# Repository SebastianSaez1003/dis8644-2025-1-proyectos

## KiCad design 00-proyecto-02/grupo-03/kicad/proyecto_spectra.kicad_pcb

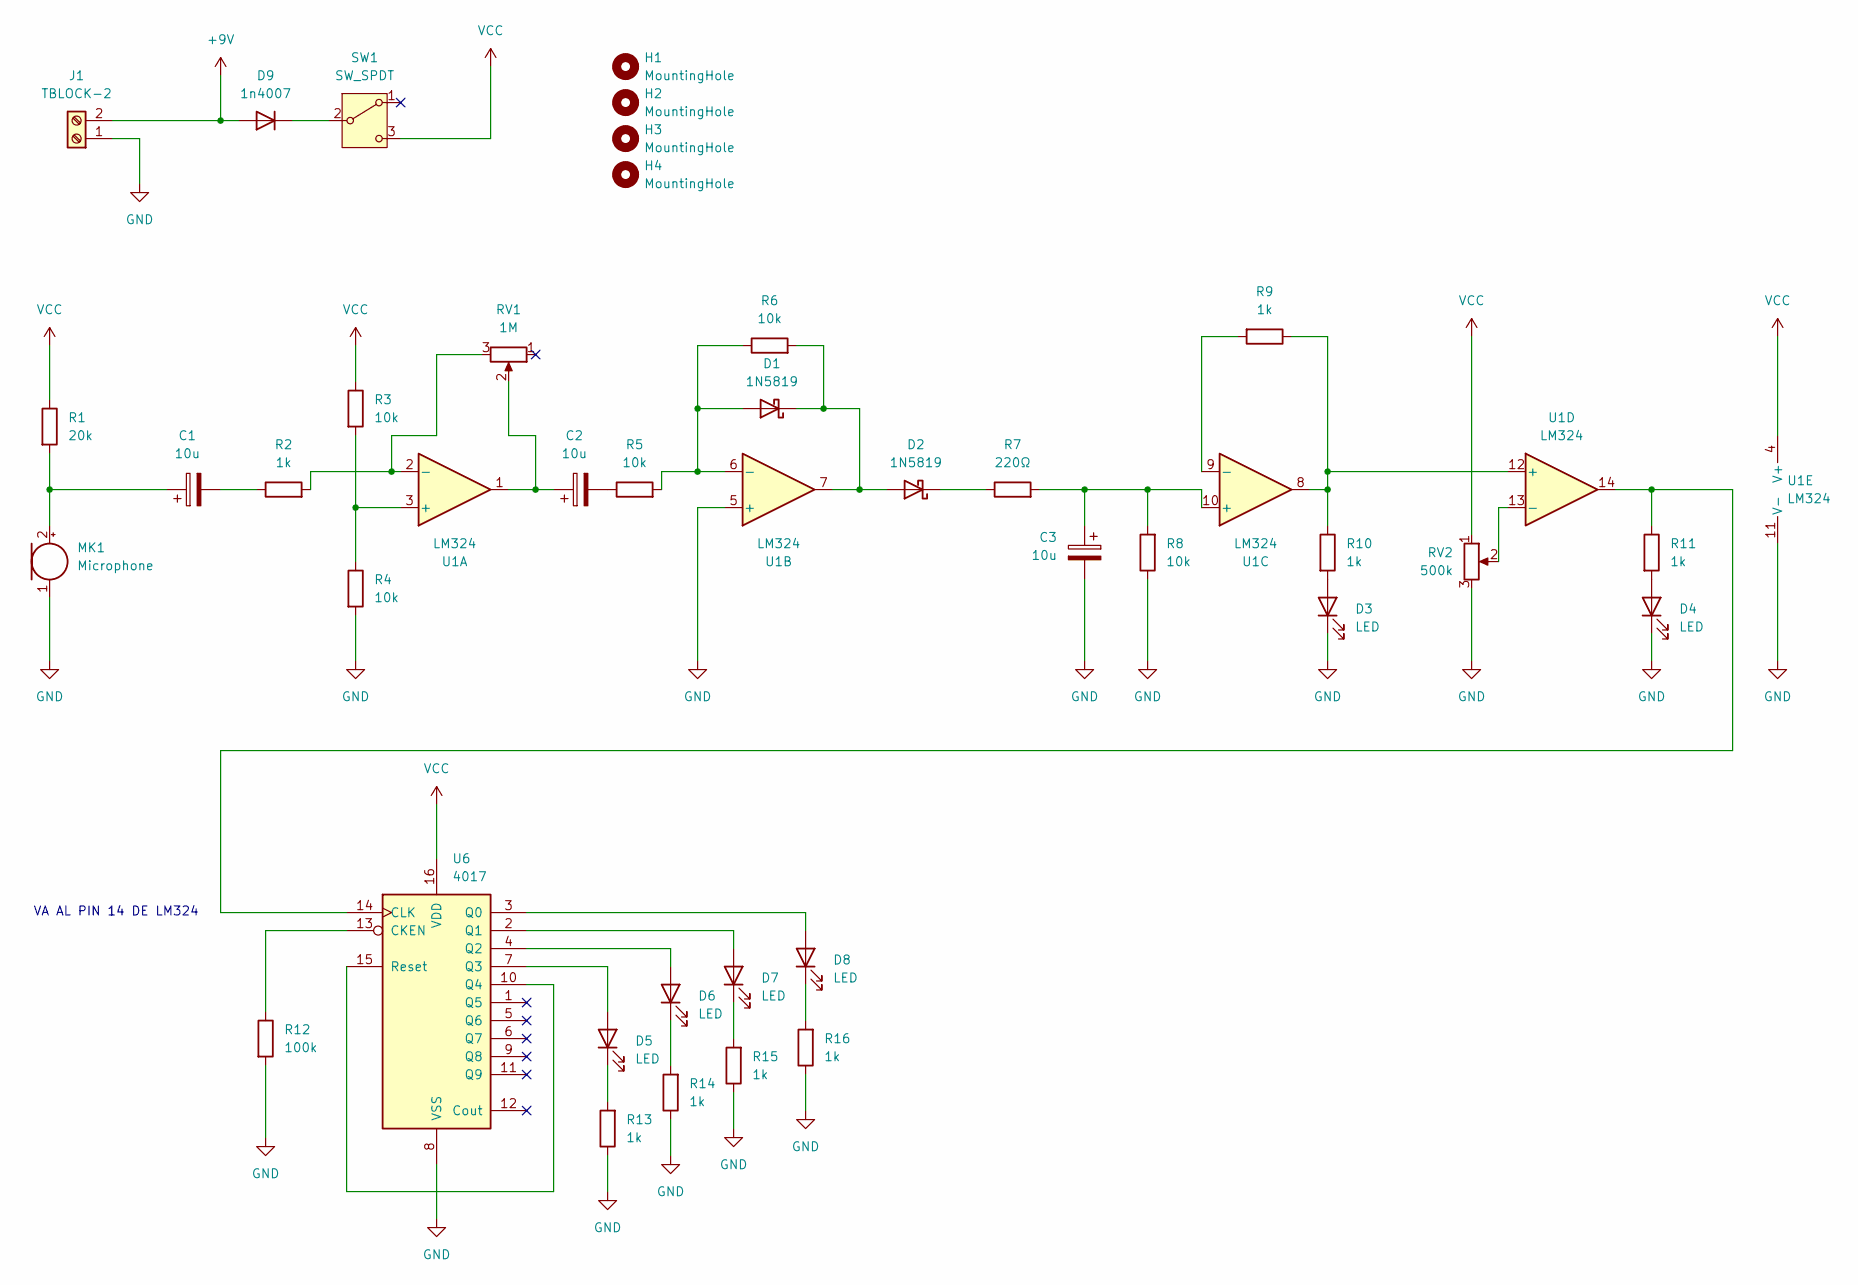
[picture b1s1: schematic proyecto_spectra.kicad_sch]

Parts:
C1, C2, C3: 10u; CP_Radial_D4.0mm_P2.00mm
D1, D2: 1N5819; D_DO-41_SOD81_P10.16mm_Horizontal
D3, D4, D5, D6, D7, D8: LED; LED_D5.0mm
D9: 1n4007; D_DO-41_SOD81_P10.16mm_Horizontal
H1, H2, H3, H4: MountingHole; MountingHole_2.1mm
J1: TBLOCK-2; TerminalBlock_MaiXu_MX126-5.0-02P_1x02_P5.00mm
MK1: Microphone; POM-2244P-C3310-2-R
R1: 20k; R_Axial_DIN0204_L3.6mm_D1.6mm_P5.08mm_Horizontal
R2, R9, R10, R11, R13, R14, R15, R16: 1k; R_Axial_DIN0204_L3.6mm_D1.6mm_P5.08mm_Horizontal
R3, R4, R5, R6, R8: 10k; R_Axial_DIN0204_L3.6mm_D1.6mm_P5.08mm_Horizontal
R7: 220Ω; R_Axial_DIN0204_L3.6mm_D1.6mm_P5.08mm_Horizontal
R12: 100k; R_Axial_DIN0204_L3.6mm_D1.6mm_P5.08mm_Horizontal
RV1: 1M; Potentiometer_Piher_T-16H_Single_Horizontal
RV2: 500k; Potentiometer_Piher_T-16H_Single_Horizontal
SW1: SW_SPDT; SPDT_PCB_small_P2.5mm
U1: LM324; DIP-14_W7.62mm
U6: 4017; DIP-16_W7.62mm

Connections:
+9V: D9.2 (A), J1.2
GND: C3.2, D3.1 (K), D4.1 (K), J1.1, MK1.1 (-), R4.2, R8.1, R12.2, R13.1, R14.1, R15.1, R16.1, RV2.3, U1.5 (+), U1.11 (V-), U6.8 (VSS)
unnamed: C1.2, R2.1
unnamed: C2.1, RV1.2, U1.1
unnamed: C2.2, R5.1
unnamed: D1.2 (A), R5.2, R6.1, U1.6 (-)
unnamed: D1.1 (K), D2.2 (A), R6.2, U1.7
unnamed: D2.1 (K), R7.1
unnamed: D3.2 (A), R10.2
unnamed: D4.2 (A), R11.2
unnamed: D5.2 (A), U6.7 (Q3)
unnamed: D5.1 (K), R13.2
unnamed: D6.2 (A), U6.4 (Q2)
unnamed: D6.1 (K), R14.2
unnamed: D7.2 (A), U6.2 (Q1)
unnamed: D7.1 (K), R15.2
unnamed: D8.2 (A), U6.3 (Q0)
unnamed: D8.1 (K), R16.2
unnamed: D9.1 (K), SW1.2 (B)
unnamed: C1.1, MK1.2 (+), R1.2
unnamed: R3.2, R4.1, U1.3 (+)
unnamed: R2.2, RV1.3, U1.2 (-)
unnamed: C3.1, R7.2, R8.2, U1.10 (+)
unnamed: R9.2, U1.9 (-)
unnamed: R9.1, R10.1, U1.8, U1.12 (+)
unnamed: RV2.2, U1.13 (-)
unnamed: R12.1, U6.13 (CKEN)
unnamed: R11.1, U1.14, U6.14 (CLK)
unnamed: U6.10 (Q4), U6.15 (Reset)
VCC: R1.1, R3.1, RV2.1, SW1.3 (C), U1.4 (V+), U6.16 (VDD)

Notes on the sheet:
VA AL PIN 14 DE LM324

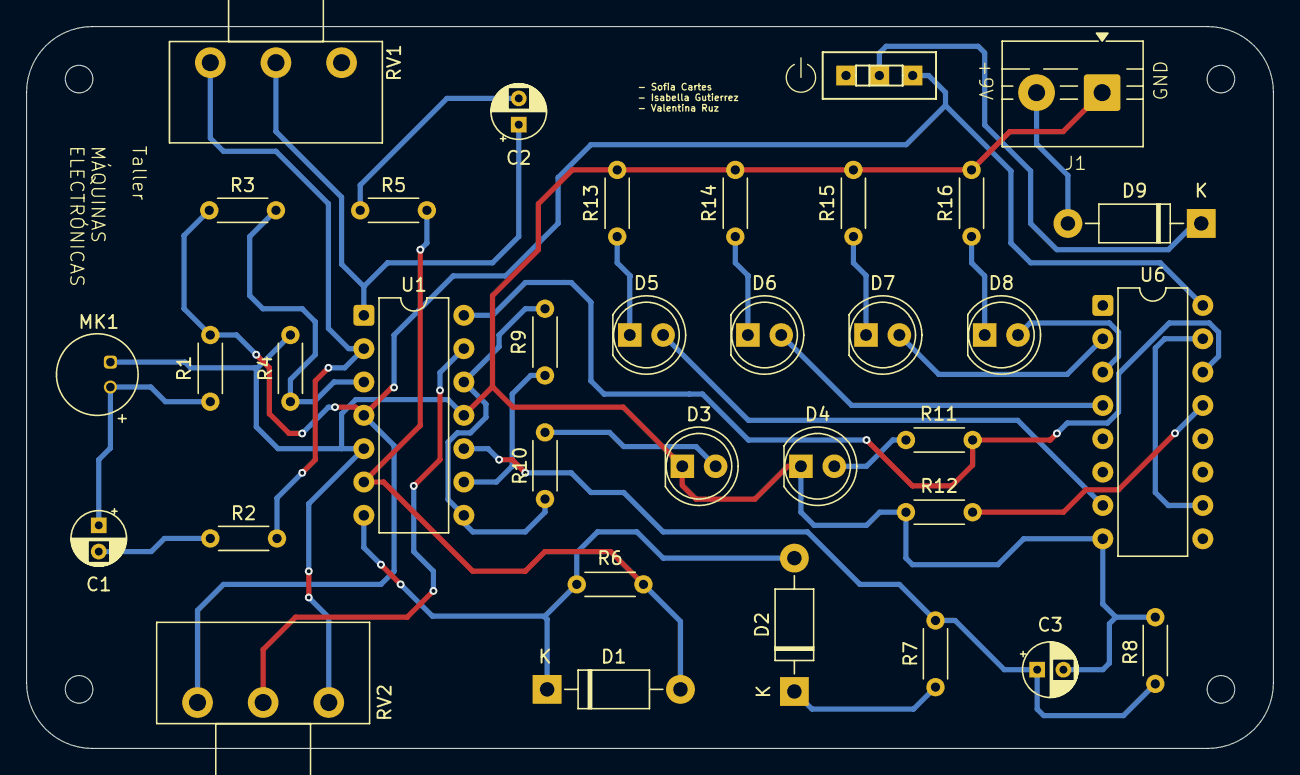
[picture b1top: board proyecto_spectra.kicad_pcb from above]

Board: 2 copper layers, 95.0 x 55.0 mm, 39 parts (0 on the bottom side), 30 nets.

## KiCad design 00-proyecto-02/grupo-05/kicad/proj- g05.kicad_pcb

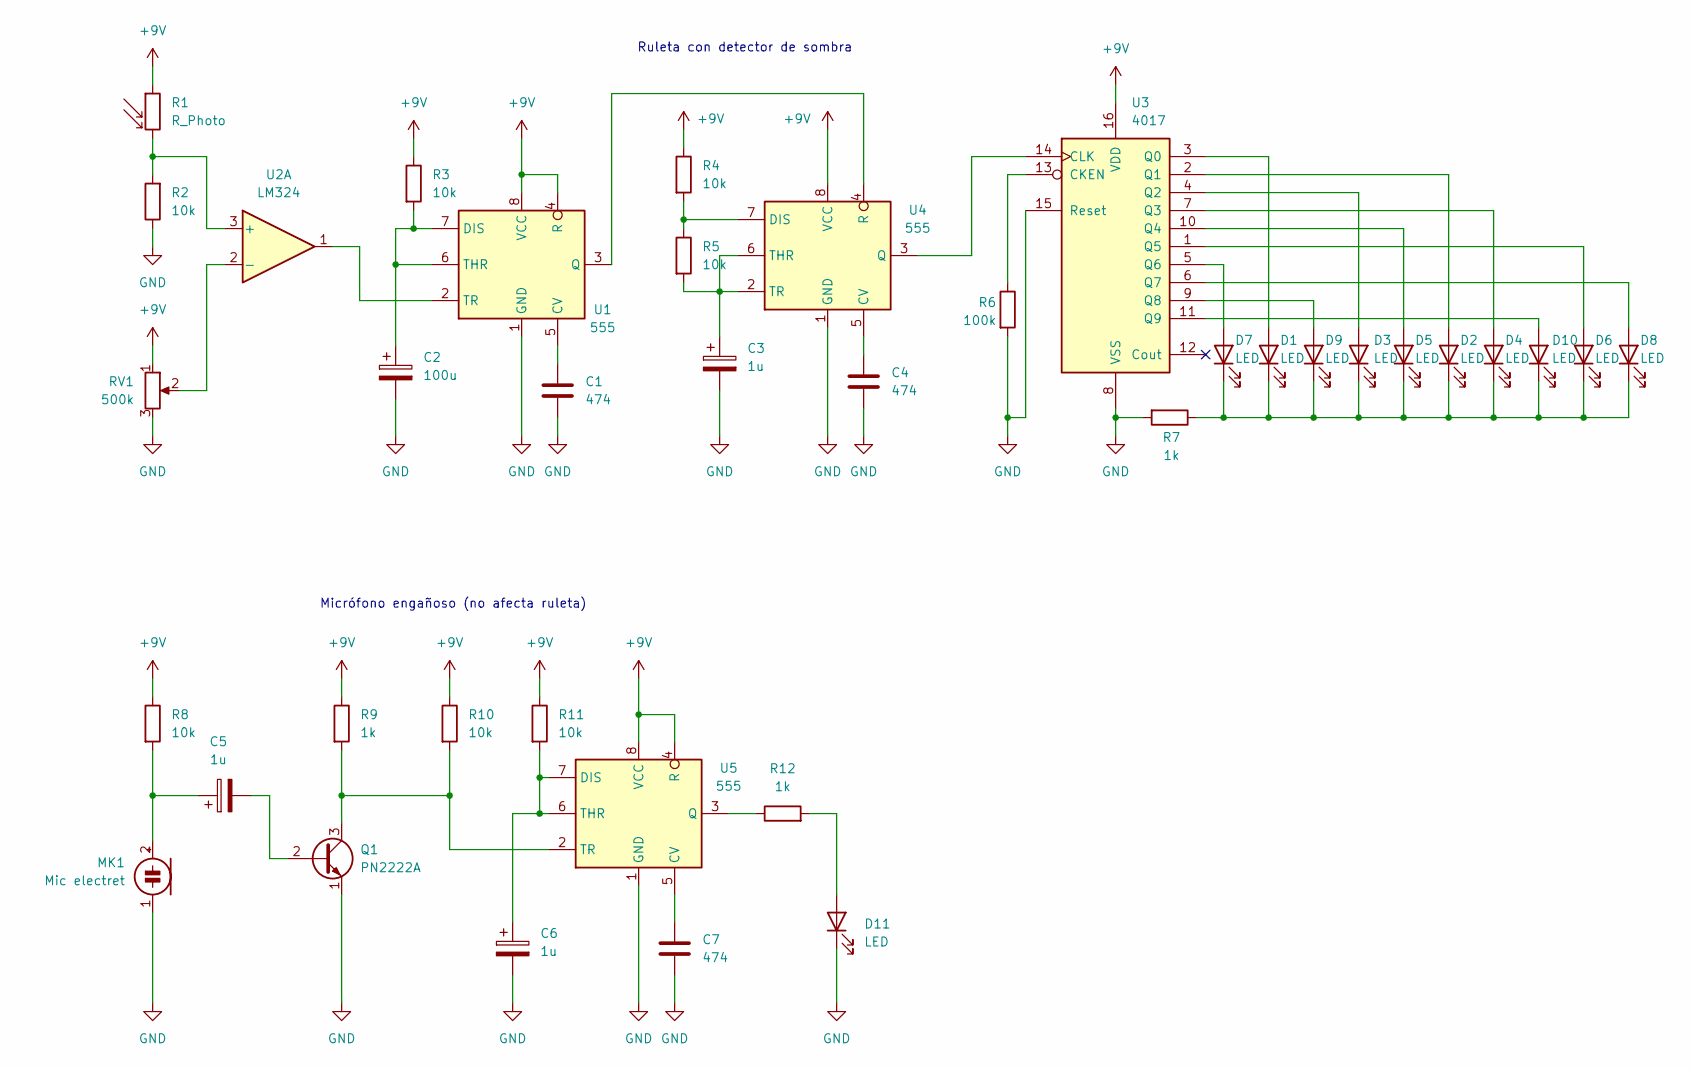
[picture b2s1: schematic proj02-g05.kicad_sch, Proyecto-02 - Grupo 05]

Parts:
C1, C4, C7: 474; C_Disc_D5.0mm_W2.5mm_P5.00mm
C2: 100u; CP_Radial_D6.3mm_P2.50mm
C3, C5, C6: 1u; CP_Radial_D6.3mm_P2.50mm
D1, D2, D3, D4, D5, D6, D7, D8, D9, D10, D11: LED; LED_D5.0mm
MK1: Mic electret; POM-2244P-C3310-2-R
Q1: PN2222A; TO-92_Inline_Wide
R1: R_Photo; R_LDR_5.1x4.3mm_P3.4mm_Vertical
R2, R3, R4, R5, R8, R10, R11: 10k; R_Axial_DIN0207_L6.3mm_D2.5mm_P10.16mm_Horizontal
R6: 100k; R_Axial_DIN0207_L6.3mm_D2.5mm_P10.16mm_Horizontal
R7, R9, R12: 1k; R_Axial_DIN0207_L6.3mm_D2.5mm_P10.16mm_Horizontal
RV1: 500k; Potentiometer_Piher_T-16H_Single_Horizontal
U1, U4, U5: 555; DIP-8_W7.62mm_Socket_LongPads
U2: LM324; DIP-14_W7.62mm_Socket_LongPads
U3: 4017; DIP-16_W7.62mm_Socket_LongPads

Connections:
+9V: R1.1, R3.1, R4.1, R8.1, R9.1, R10.1, R11.1, RV1.1, U1.4 (R), U1.8 (VCC), U3.16 (VDD), U4.8 (VCC), U5.4 (R), U5.8 (VCC)
GND: C1.2, C2.2, C3.2, C4.2, C6.2, C7.2, D11.1 (K), MK1.1 (-), Q1.1 (E), R2.1, R6.2, R7.2, RV1.3, U1.1 (GND), U3.8 (VSS), U3.15 (Reset), U4.1 (GND), U5.1 (GND)
unnamed: D1.2 (A), U3.3 (Q0)
unnamed: D1.1 (K), D2.1 (K), D3.1 (K), D4.1 (K), D5.1 (K), D6.1 (K), D7.1 (K), D8.1 (K), D9.1 (K), D10.1 (K), R7.1
unnamed: D2.2 (A), U3.2 (Q1)
unnamed: D3.2 (A), U3.4 (Q2)
unnamed: D4.2 (A), U3.7 (Q3)
unnamed: D5.2 (A), U3.10 (Q4)
unnamed: D6.2 (A), U3.1 (Q5)
unnamed: D7.2 (A), U3.5 (Q6)
unnamed: D8.2 (A), U3.6 (Q7)
unnamed: D9.2 (A), U3.9 (Q8)
unnamed: D10.2 (A), U3.11 (Q9)
unnamed: D11.2 (A), R12.2
unnamed: C5.1, MK1.2 (+), R8.2
unnamed: C5.2, Q1.2 (B)
unnamed: Q1.3 (C), R9.2, R10.2, U5.2 (TR)
unnamed: C1.1, U1.5 (CV)
unnamed: C2.1, R3.2, U1.6 (THR), U1.7 (DIS)
unnamed: U1.3 (Q), U4.4 (R)
unnamed: U1.2 (TR), U2.1
unnamed: R1.2, R2.2, U2.3 (+)
unnamed: RV1.2, U2.2 (-)
unnamed: R6.1, U3.13 (CKEN)
unnamed: U3.14 (CLK), U4.3 (Q)
unnamed: C4.1, U4.5 (CV)
unnamed: R4.2, R5.1, U4.7 (DIS)
unnamed: C3.1, R5.2, U4.2 (TR), U4.6 (THR)
unnamed: C7.1, U5.5 (CV)
unnamed: C6.1, R11.2, U5.6 (THR), U5.7 (DIS)
unnamed: R12.1, U5.3 (Q)

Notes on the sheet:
Micrófono engañoso (no afecta ruleta)
Ruleta con detector de sombra

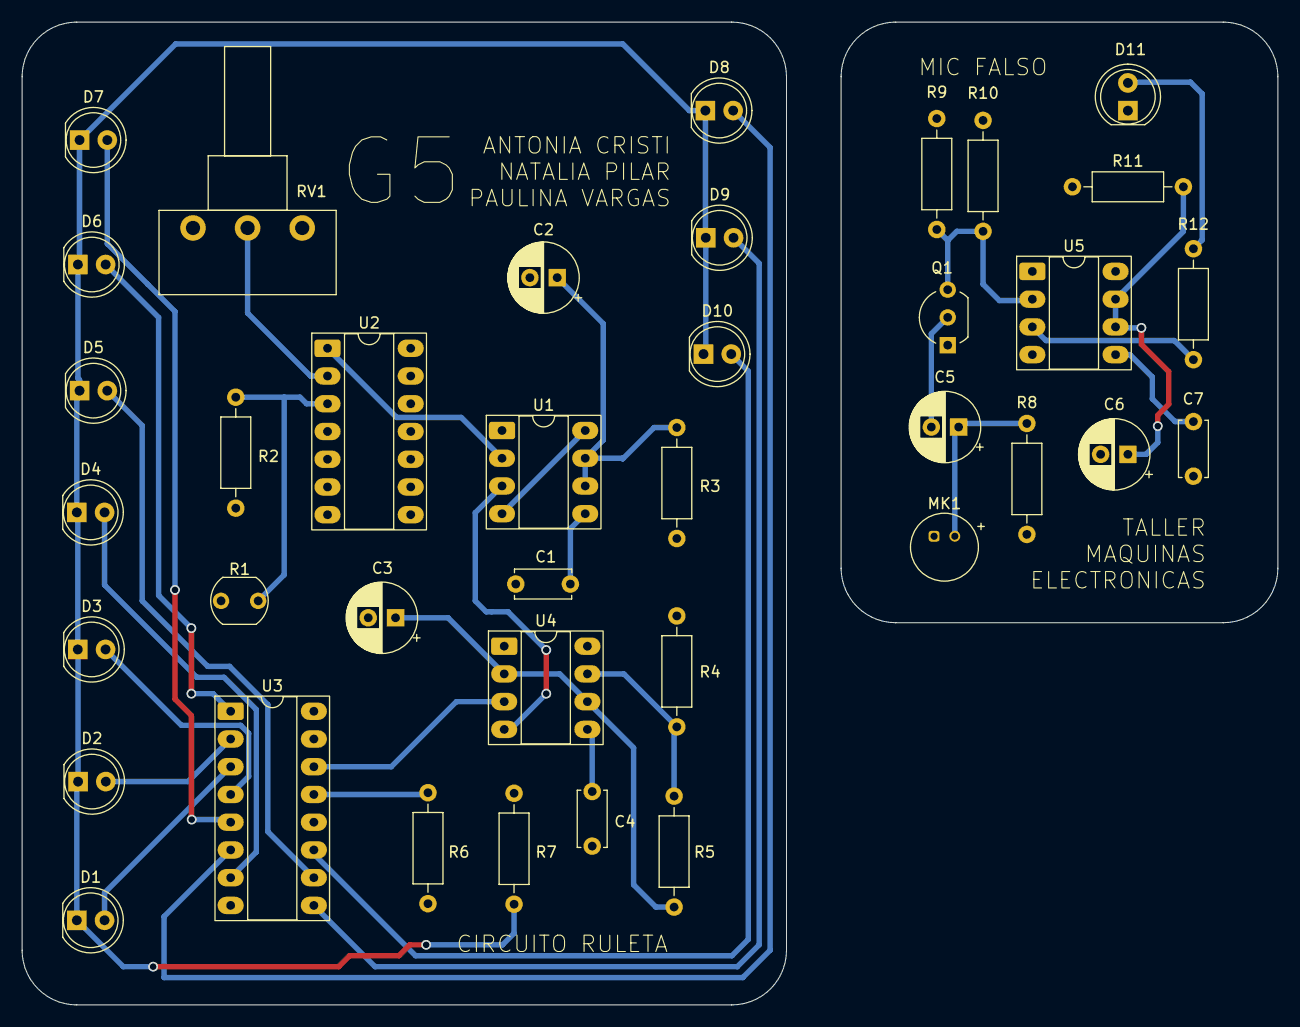
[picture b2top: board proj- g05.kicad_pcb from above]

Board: 2 copper layers, 115.0 x 90.0 mm, 38 parts (0 on the bottom side), 31 nets.

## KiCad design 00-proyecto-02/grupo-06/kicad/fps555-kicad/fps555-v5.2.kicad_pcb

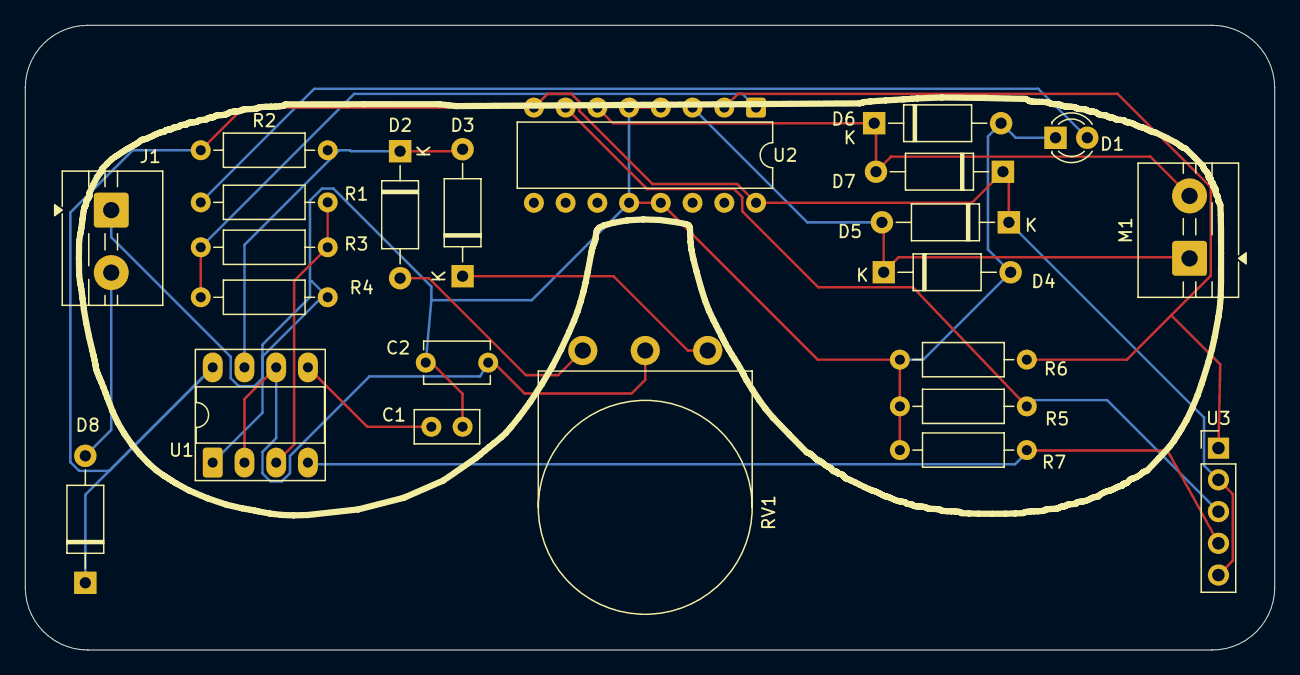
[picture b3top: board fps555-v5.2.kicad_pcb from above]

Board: 2 copper layers, 100.0 x 50.0 mm, 23 parts (0 on the bottom side), 16 nets.

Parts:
C1: 100n; C_Disc_D5.0mm_W2.5mm_P2.50mm
C2: 470p; C_Disc_D5.1mm_W3.2mm_P5.00mm
D1: LED; LED_D3.0mm_Clear
D2, D3, D4, D5, D6, D7, D8: 4007; D_A-405_P10.16mm_Horizontal
J1: Batería 9v; TerminalBlock_MaiXu_MX126-5.0-02P_1x02_P5.00mm
M1: Motorreductor; TerminalBlock_MaiXu_MX126-5.0-02P_1x02_P5.00mm
R1, R3: 1k; R_Axial_DIN0207_L6.3mm_D2.5mm_P10.16mm_Horizontal
R2: 10k; R_Axial_DIN0207_L6.3mm_D2.5mm_P10.16mm_Horizontal
R4, R7: 100k; R_Axial_DIN0207_L6.3mm_D2.5mm_P10.16mm_Horizontal
R5, R6: 470k; R_Axial_DIN0207_L6.3mm_D2.5mm_P10.16mm_Horizontal
RV1: 500k; Potentiometer_Omeg_PC16BU_Vertical
U1: 555; DIP-8_W7.62mm_Socket_LongPads
U2: L293D; DIP-16_W7.62mm
U3: mst303; PinHeader_1x05_P2.54mm_Vertical

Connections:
+9V: D8.2 (A), J1.2
GND: C1.2, C2.2, D1.1 (K), D4.2 (A), D6.2 (A), J1.1, R4.2, R5.1, R6.1, R7.1, U1.1 (GND), U2.4 (GND), U2.5 (GND), U2.12 (GND), U2.13 (GND)
unnamed: D1.2 (A), R1.2
unnamed: D2.2 (A), RV1.1
unnamed: D2.1 (K), D3.2 (A), R2.2, U1.7 (DIS)
unnamed: D3.1 (K), RV1.3
unnamed: D4.1 (K), D5.2 (A), M1.1 (+), U2.3 (1Y)
unnamed: D6.1 (K), D7.2 (A), M1.2 (-), U2.6 (2Y)
unnamed: C1.1, U1.5 (CV)
unnamed: R1.1, R3.1, U1.3 (Q)
unnamed: R7.2, U1.4 (R), U3.4
unnamed: C2.1, RV1.2, U1.2 (TR), U1.6 (THR)
unnamed: R6.2, U2.2 (1A), U3.1
unnamed: R5.2, U2.7 (2A), U3.3
unnamed: R3.2, R4.1, U2.1 (EN1,2)
VCC: D5.1 (K), D7.1 (K), D8.1 (K), R2.1, U1.8 (VCC), U2.8 (VCC2), U2.16 (VCC1), U3.2, U3.5
